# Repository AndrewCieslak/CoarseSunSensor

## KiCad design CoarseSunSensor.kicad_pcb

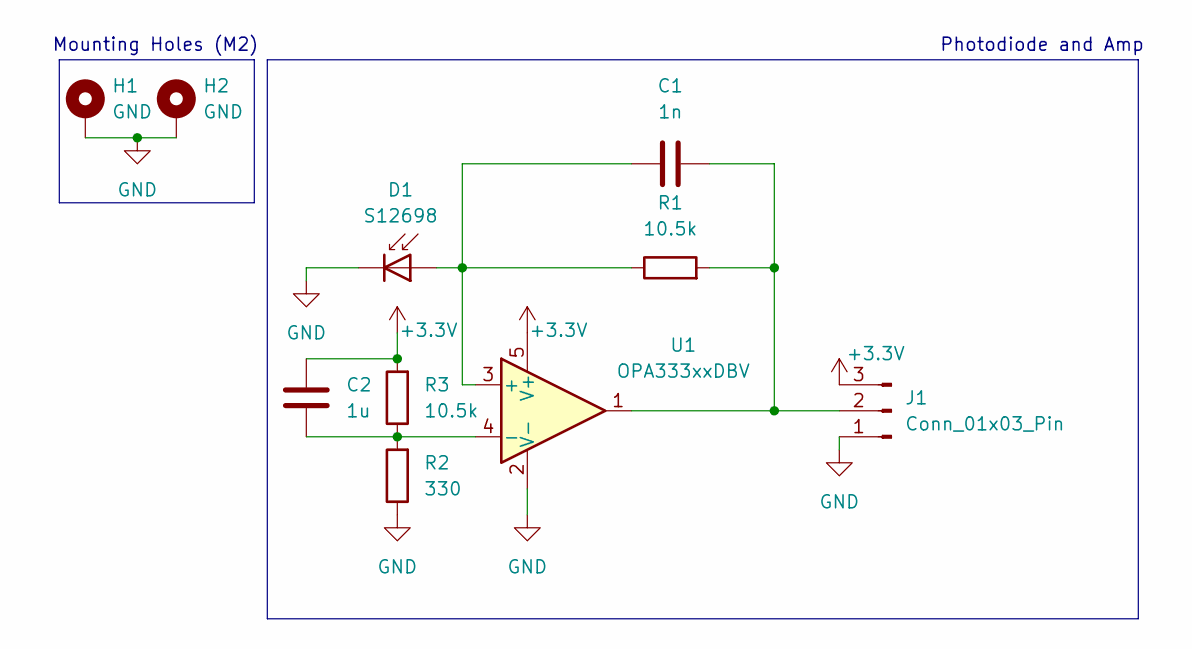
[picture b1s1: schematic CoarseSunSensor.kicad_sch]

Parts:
C1: 1n; C_0402_1005Metric
C2: 1u; C_0603_1608Metric
D1: S12698; TO-18-3_Window
H1, H2: GND; MountingHole_2.2mm_M2_DIN965_Pad_TopOnly
J1: Conn_01x03_Pin; PinHeader_1x03_P1.00mm_Horizontal
R1, R3: 10.5k; R_0402_1005Metric
R2: 330; R_0402_1005Metric
U1: OPA333xxDBV; SOT-23-5

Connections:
+3.3V: C2.1, J1.3, R3.2, U1.5 (V+)
GND: D1.1 (K), H1.1 (1_1), H2.1 (1_1), J1.1, R2.1, U1.2 (V-)
unnamed: C1.1, D1.2 (A), R1.1, U1.3 (+)
unnamed: C1.2, J1.2, R1.2, U1.1
unnamed: C2.2, R2.2, R3.1, U1.4 (-)

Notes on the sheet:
Mounting Holes (M2)
Photodiode and Amp

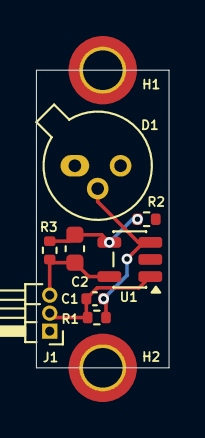
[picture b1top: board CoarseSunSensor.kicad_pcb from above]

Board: 2 copper layers, 7.4 x 16.5 mm, 10 parts (0 on the bottom side), 5 nets.
